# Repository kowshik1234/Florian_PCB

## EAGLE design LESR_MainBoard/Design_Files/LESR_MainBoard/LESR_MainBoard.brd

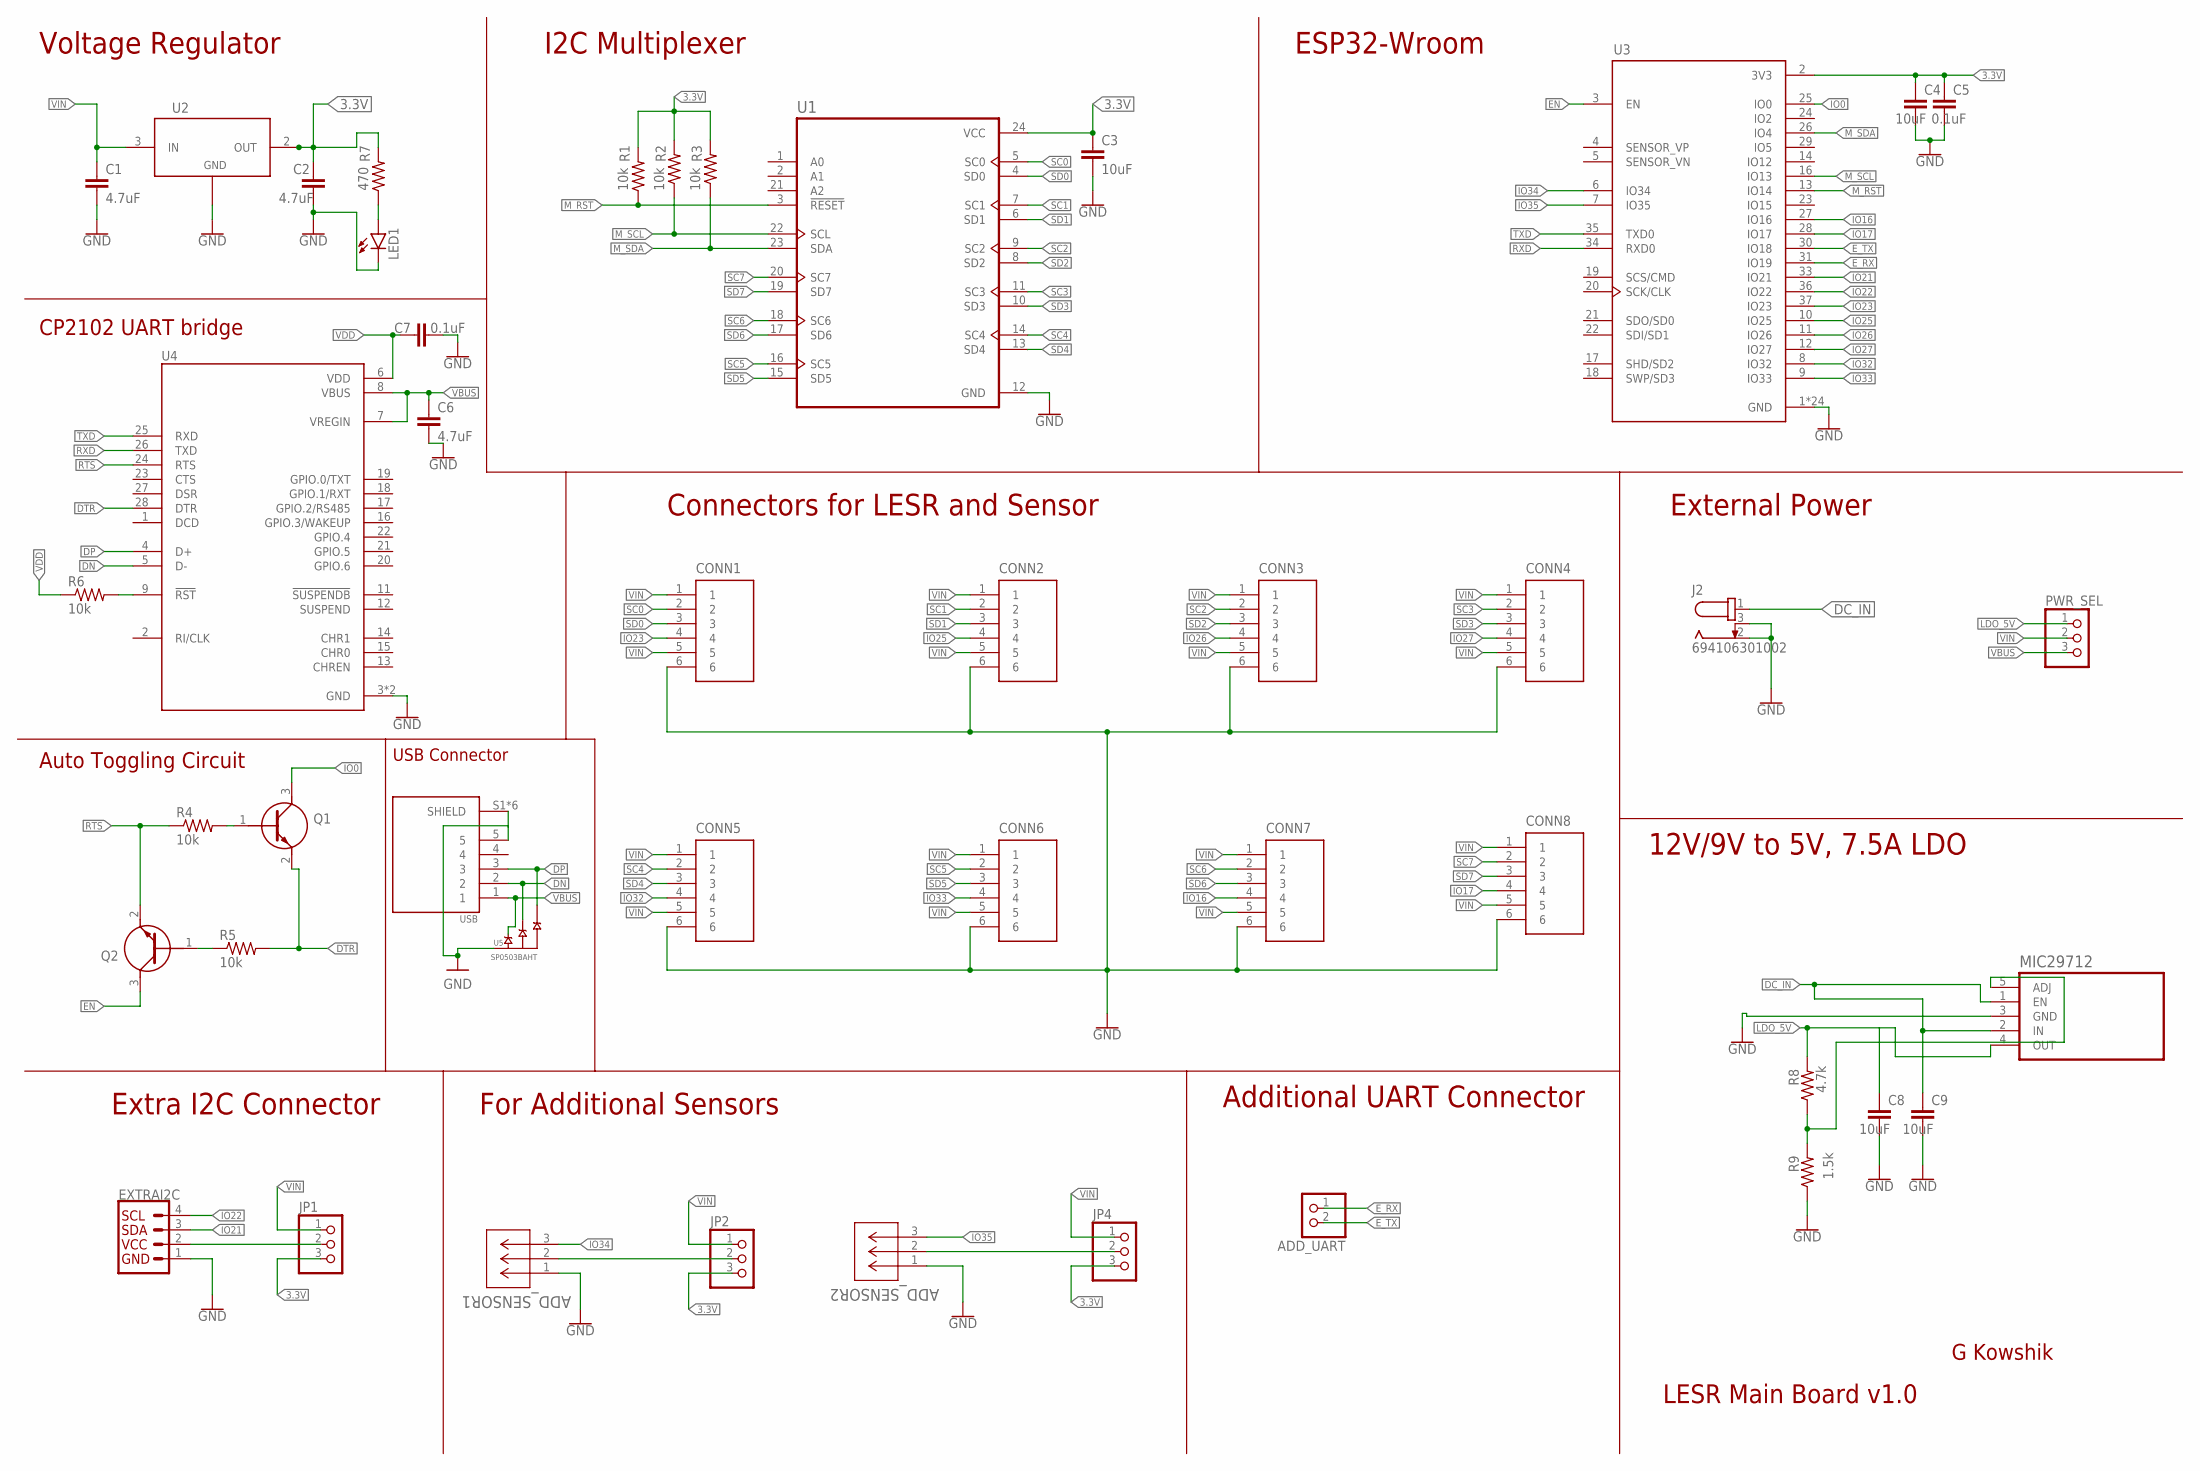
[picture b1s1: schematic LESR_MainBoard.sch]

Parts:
ADD_SENSOR1, ADD_SENSOR2: BM03B-SRSS-TB(LF)(SN); CONN_BM03B-SRSS-TB(LF)(SN)_JST
ADD_UART: JST_2PIN-SMT; JST-PH-2-SMT
C1, C2, C6: 4.7uF; C0805
C3, C4, C8, C9: 10uF; C0805
C5, C7: 0.1uF; C0805
CONN1, CONN2, CONN3, CONN4, CONN5, CONN6, CONN7, CONN8: JST_6_PIN_VERTICAL; JST-6-SMD-VERT-1.0MM
EXTRAI2C: Vertical Qwiic Connector; JST04_1MM_VERT
J2: 694106301002
JP1, JP2, JP4: PINHD-1X3; 1X03
LED1: LEDCHIPLED_0805; CHIPLED_0805
MIC29712: MIC29712WT; TO170P1066X482X1572-5
PWR_SEL: PINHD-1X3; 1X03
Q1, Q2: SS8050-G; SOT95P240X115-3N
R1, R2, R3, R4, R5, R6: 10k; R0805
R7: 470; R0805
R8: 4.7k; R0805
R9: 1.5k; R0805
U1: TCA9548APWR; SOP65P640X120-24N
U2: NCP1117ST33T3G; SOT-223
U3: ESP32-WROOM-32; MODULE_ESP32-WROOM-32
U4: CP2102N-A01-GQFN28; QFN50P500X500X80-29N
U5: SP0503BAHT; SOT143
USB: 10118194-0001LF; AMPHENOL_10118194-0001LF

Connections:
3.3V: C2.1, C3.1, C4.1, C5.1, JP1.3, JP2.3, JP4.3, R1.2, R2.2, R3.2, R7.2, U1.24 (VCC), U2.2 (OUT), U2.4, U3.2 (3V3)
DC_IN: C9.1, J2.1, MIC29712.1 (EN), MIC29712.2 (IN)
DN: U4.5 (D-), U5.3 (B), USB.2
DP: U4.4 (D+), U5.4 (C), USB.3
DTR: Q1.2 (E), R5.2, U4.28 (DTR)
EN: Q2.3 (C), U3.3 (EN)
E_RX: ADD_UART.1 (2), U3.31 (IO19)
E_TX: ADD_UART.2 (1), U3.30 (IO18)
GND: ADD_SENSOR1.1, ADD_SENSOR2.1, C1.2, C2.2, C3.2, C4.2, C5.2, C6.2, C7.2, C8.2, C9.2, CONN1.6, CONN2.6, CONN3.6, CONN4.6, CONN5.6, CONN6.6, CONN7.6, CONN8.6, EXTRAI2C.1, J2.2, J2.3, LED1.C, MIC29712.3 (GND), R9.1, U1.12 (GND), U2.1 (ADJ/GND), U3.1 (GND), U3.15 (GND), U3.38 (GND), U3.39_1 (GND), U3.39_2 (GND), U3.39_3 (GND), U3.39_4 (GND), U3.39_5 (GND), U3.39_6 (GND), U3.39_7 (GND), U3.39_8 (GND), U3.39_9 (GND), U3.39_10 (GND), U3.39_11 (GND), U3.39_12 (GND), U3.39_13 (GND), U3.39_14 (GND), U3.39_15 (GND), U3.39_16 (GND), U3.39_17 (GND), U3.39_18 (GND), U3.39_19 (GND), U3.39_20 (GND), U3.39_21 (GND), U4.3 (GND), U4.29 (GND), U5.1 (GND), USB.5, USB.S1 (SHIELD), USB.S2 (SHIELD), USB.S3 (SHIELD), USB.S4 (SHIELD), USB.S5 (SHIELD), USB.S6 (SHIELD)
IO0: Q1.3 (C), U3.25 (IO0)
IO16: CONN7.4, U3.27 (IO16)
IO17: CONN8.4, U3.28 (IO17)
IO21: EXTRAI2C.3, U3.33 (IO21)
IO22: EXTRAI2C.4, U3.36 (IO22)
IO23: CONN1.4, U3.37 (IO23)
IO25: CONN2.4, U3.10 (IO25)
IO26: CONN3.4, U3.11 (IO26)
IO27: CONN4.4, U3.12 (IO27)
IO32: CONN5.4, U3.8 (IO32)
IO33: CONN6.4, U3.9 (IO33)
IO34: ADD_SENSOR1.3, U3.6 (IO34)
IO35: ADD_SENSOR2.3, U3.7 (IO35)
LDO_5V: C8.1, MIC29712.4 (OUT), PWR_SEL.1, R8.2
M_RST: R1.1, U1.3 (!RESET), U3.13 (IO14)
M_SCL: R2.1, U1.22 (SCL), U3.16 (IO13)
M_SDA: R3.1, U1.23 (SDA), U3.26 (IO4)
unnamed: ADD_SENSOR1.2, JP2.2
unnamed: MIC29712.5 (ADJ), R8.1, R9.2
unnamed: Q1.1 (B), R4.2
unnamed: Q2.1 (B), R5.1
unnamed: ADD_SENSOR2.2, JP4.2
unnamed: R6.2, U4.9 (!RST)
unnamed: EXTRAI2C.2, JP1.2
unnamed: LED1.A, R7.1
RTS: Q2.2 (E), R4.1, U4.24 (RTS)
RXD: U3.34 (RXD0), U4.26 (TXD)
SC0: CONN1.2, U1.5 (SC0)
SC1: CONN2.2, U1.7 (SC1)
SC2: CONN3.2, U1.9 (SC2)
SC3: CONN4.2, U1.11 (SC3)
SC4: CONN5.2, U1.14 (SC4)
SC5: CONN6.2, U1.16 (SC5)
SC6: CONN7.2, U1.18 (SC6)
SC7: CONN8.2, U1.20 (SC7)
SD0: CONN1.3, U1.4 (SD0)
SD1: CONN2.3, U1.6 (SD1)
SD2: CONN3.3, U1.8 (SD2)
SD3: CONN4.3, U1.10 (SD3)
SD4: CONN5.3, U1.13 (SD4)
SD5: CONN6.3, U1.15 (SD5)
SD6: CONN7.3, U1.17 (SD6)
SD7: CONN8.3, U1.19 (SD7)
TXD: U3.35 (TXD0), U4.25 (RXD)
VBUS: C6.1, PWR_SEL.3, U4.7 (VREGIN), U4.8 (VBUS), U5.2 (A), USB.1
VDD: C7.1, R6.1, U4.6 (VDD)
VIN: C1.1, CONN1.1, CONN1.5, CONN2.1, CONN2.5, CONN3.1, CONN3.5, CONN4.1, CONN4.5, CONN5.1, CONN5.5, CONN6.1, CONN6.5, CONN7.1, CONN7.5, CONN8.1, CONN8.5, JP1.1, JP2.1, JP4.1, PWR_SEL.2, U2.3 (IN)

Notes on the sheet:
Voltage Regulator
LESR Main Board v1.0
G Kowshik
I2C Multiplexer
ESP32-Wroom
CP2102 UART bridge
Auto Toggling Circuit
USB Connector
Extra I2C Connector
For Additional Sensors
Additional UART Connector
External Power
Connectors for LESR and Sensor
12V/9V to 5V, 7.5A LDO

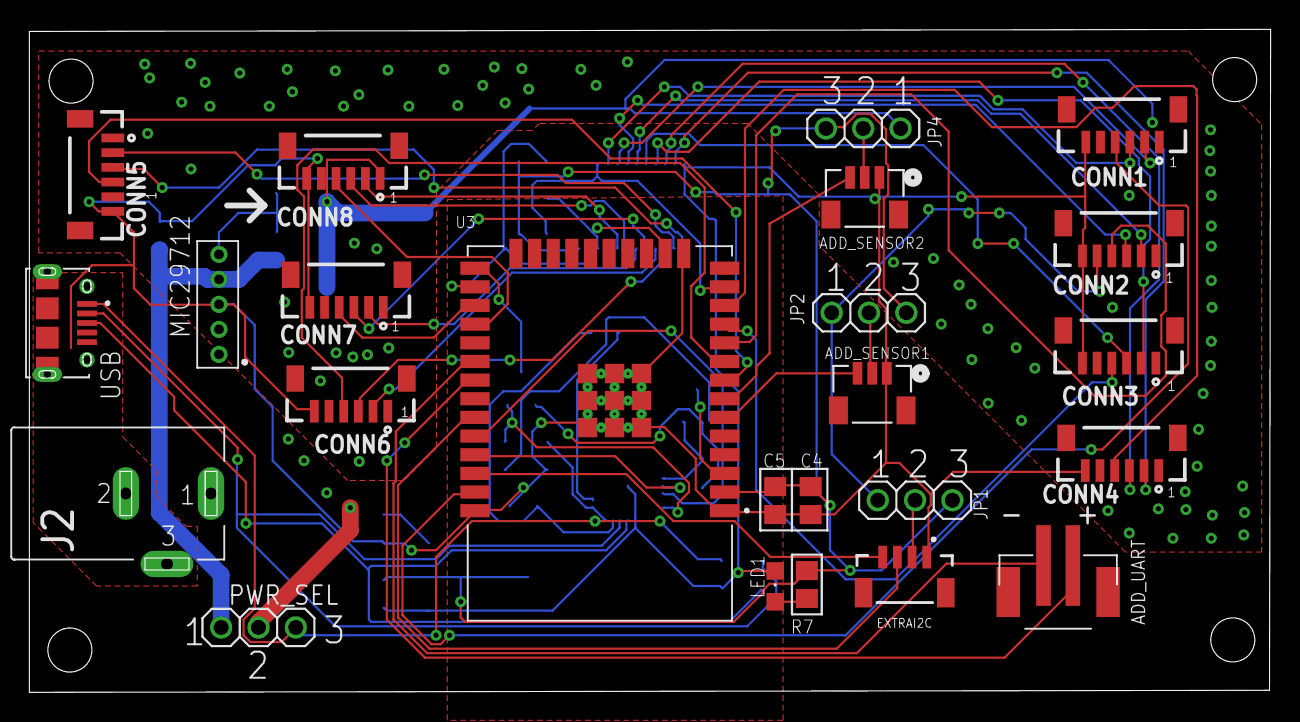
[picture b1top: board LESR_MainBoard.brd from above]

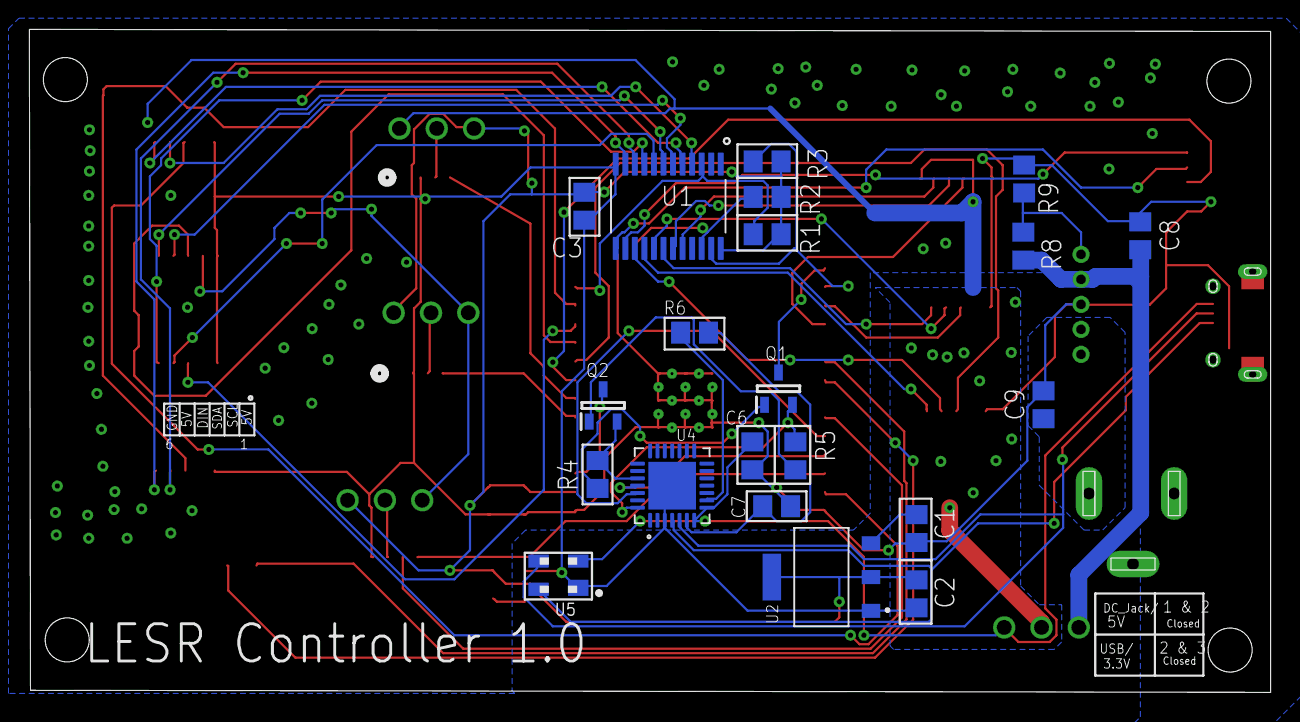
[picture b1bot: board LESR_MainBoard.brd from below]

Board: 2 copper layers, 84.5 x 45.1 mm, 45 parts (21 on the bottom side), 56 nets.

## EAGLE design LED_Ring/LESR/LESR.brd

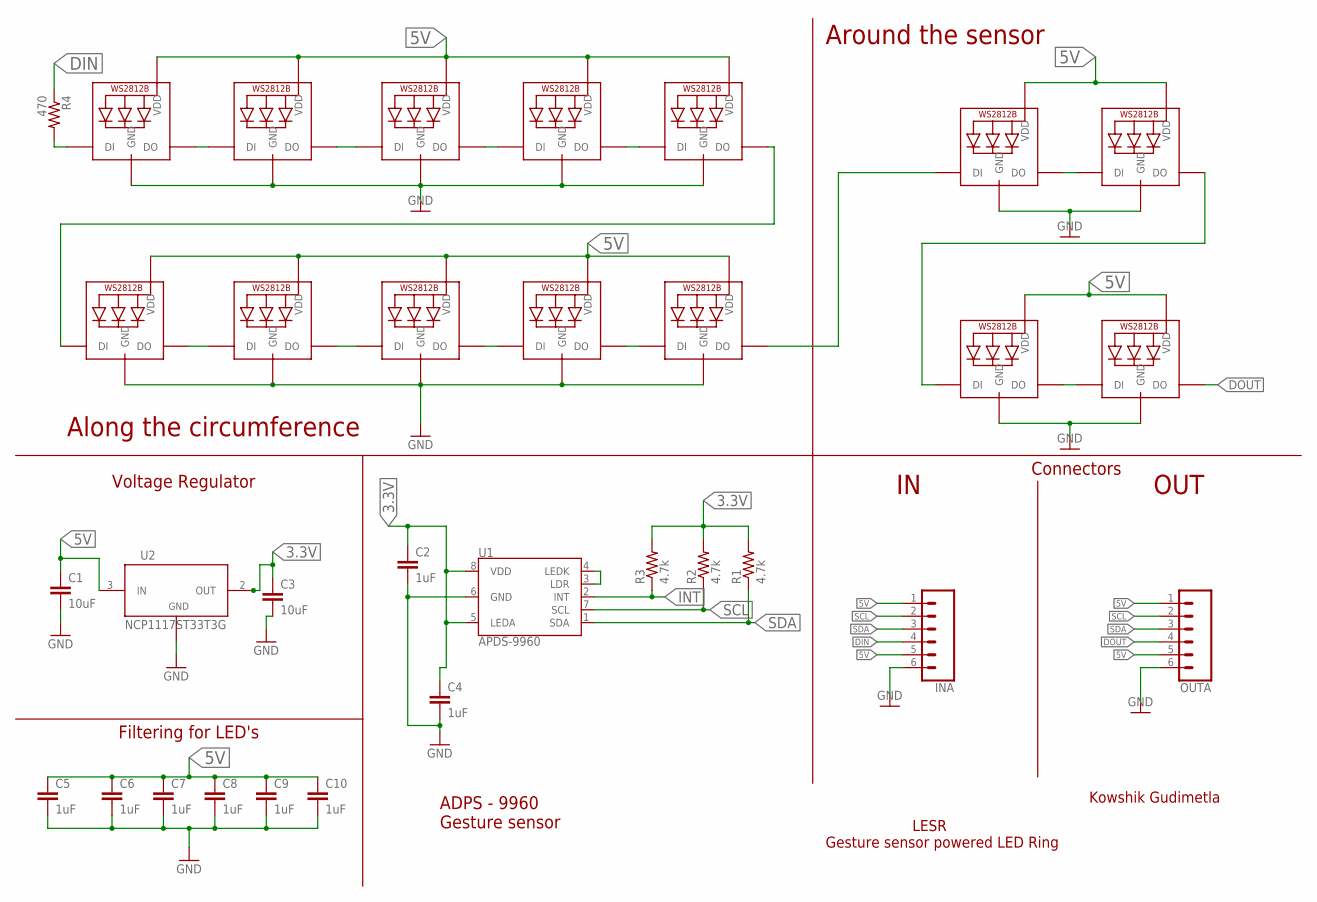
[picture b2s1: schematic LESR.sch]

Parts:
C1, C3: 10uF; C0603
C2, C4, C5, C6, C7, C8, C9, C10: 1uF; C0603
IN: BM06B-SRSS-TB; JST-6-SMD-HORI-1.0MM
LED1, LED2, LED3, LED4, LED5, LED6, LED7, LED8, LED9, LED10, LED11, LED12, LED13, LED14: WS2812B5050; WS2812B
OUT: BM06B-SRSS-TB; JST-6-SMD-HORI-1.0MM
R1, R2, R3: 4.7k; R0603
R4: 470; R0603
U1: APDS-9960
U2: NCP1117ST33T3G; SOT-223

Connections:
3.3V: C2.1, C3.1, C4.1, R1.2, R2.2, R3.2, U1.5 (LEDA), U1.8 (VDD), U2.2 (OUT), U2.4
5V: C1.1, C5.1, C6.1, C7.1, C8.1, C9.1, C10.1, IN.1, IN.5, LED1.1-VDD (VDD), LED2.1-VDD (VDD), LED3.1-VDD (VDD), LED4.1-VDD (VDD), LED5.1-VDD (VDD), LED6.1-VDD (VDD), LED7.1-VDD (VDD), LED8.1-VDD (VDD), LED9.1-VDD (VDD), LED10.1-VDD (VDD), LED11.1-VDD (VDD), LED12.1-VDD (VDD), LED13.1-VDD (VDD), LED14.1-VDD (VDD), OUT.1, OUT.5, U2.3 (IN)
DIN: IN.4, R4.1
DOUT: LED14.2-DOUT (DO), OUT.4
GND: C1.2, C2.2, C3.2, C4.2, C5.2, C6.2, C7.2, C8.2, C9.2, C10.2, IN.6, LED1.3-GND (GND), LED2.3-GND (GND), LED3.3-GND (GND), LED4.3-GND (GND), LED5.3-GND (GND), LED6.3-GND (GND), LED7.3-GND (GND), LED8.3-GND (GND), LED9.3-GND (GND), LED10.3-GND (GND), LED11.3-GND (GND), LED12.3-GND (GND), LED13.3-GND (GND), LED14.3-GND (GND), OUT.6, U1.6 (GND), U2.1 (ADJ/GND)
INT: R3.1, U1.2 (INT)
unnamed: LED1.4-DIN (DI), R4.2
unnamed: U1.3 (LDR), U1.4 (LEDK)
unnamed: LED6.2-DOUT (DO), LED7.4-DIN (DI)
unnamed: LED7.2-DOUT (DO), LED8.4-DIN (DI)
unnamed: LED8.2-DOUT (DO), LED9.4-DIN (DI)
unnamed: LED9.2-DOUT (DO), LED10.4-DIN (DI)
unnamed: LED1.2-DOUT (DO), LED2.4-DIN (DI)
unnamed: LED2.2-DOUT (DO), LED3.4-DIN (DI)
unnamed: LED3.2-DOUT (DO), LED4.4-DIN (DI)
unnamed: LED4.2-DOUT (DO), LED5.4-DIN (DI)
unnamed: LED11.2-DOUT (DO), LED12.4-DIN (DI)
unnamed: LED13.2-DOUT (DO), LED14.4-DIN (DI)
unnamed: LED12.2-DOUT (DO), LED13.4-DIN (DI)
unnamed: LED5.2-DOUT (DO), LED6.4-DIN (DI)
unnamed: LED10.2-DOUT (DO), LED11.4-DIN (DI)
SCL: IN.2, OUT.2, R2.1, U1.7 (SCL)
SDA: IN.3, OUT.3, R1.1, U1.1 (SDA)

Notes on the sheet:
Kowshik Gudimetla
LESR Gesture sensor powered LED Ring
Voltage Regulator
ADPS - 9960 Gesture sensor
Along the circumference
Around the sensor
Connectors
Filtering for LED's
OUT

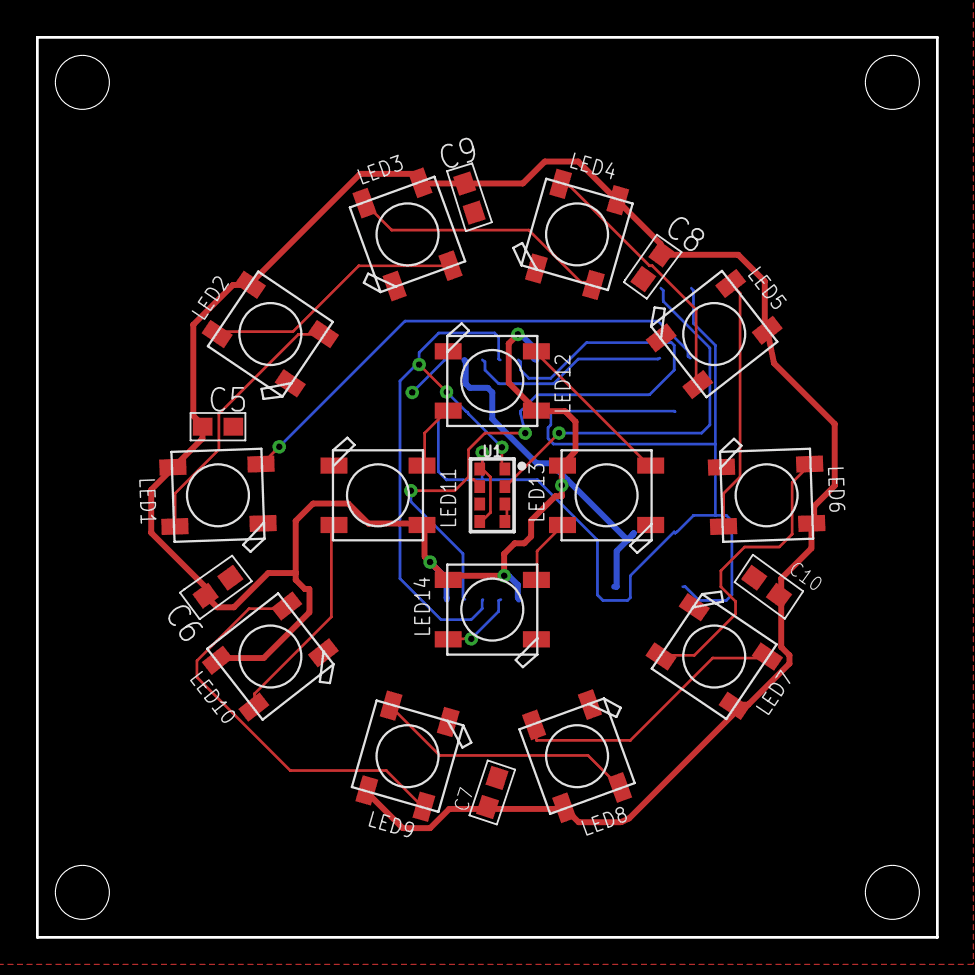
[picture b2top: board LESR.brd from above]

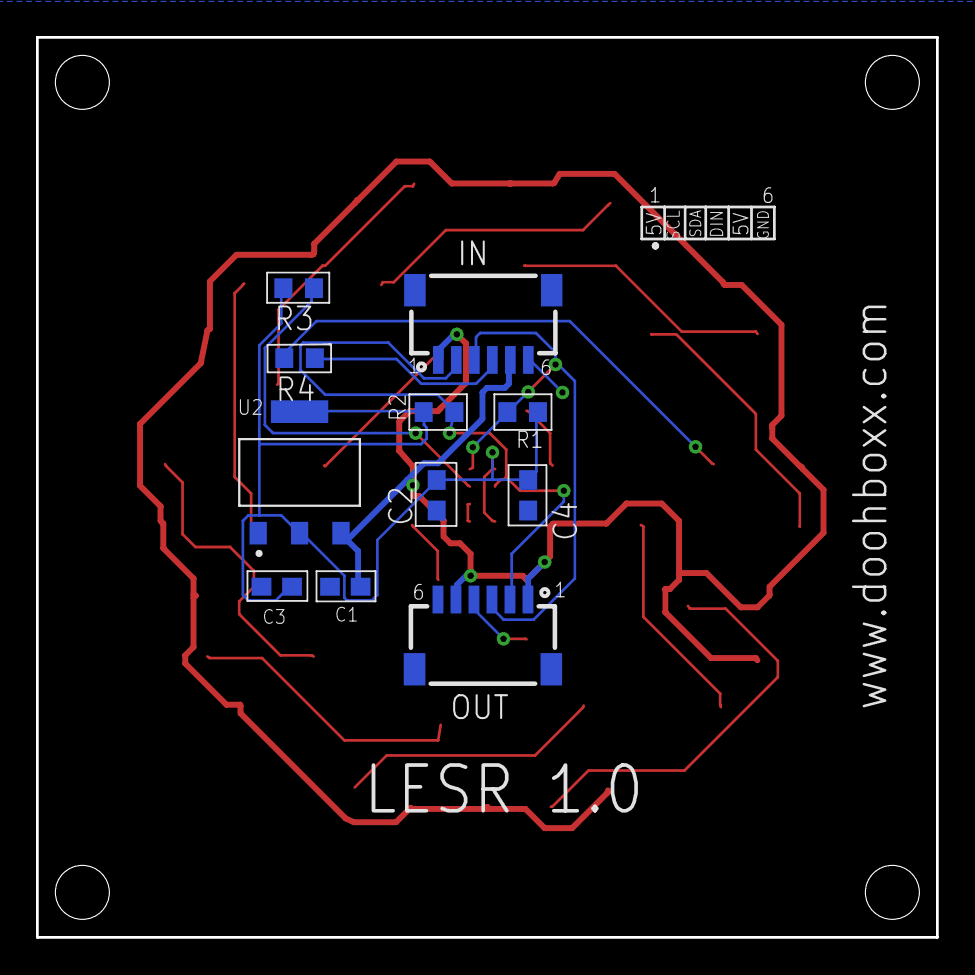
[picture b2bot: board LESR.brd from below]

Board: 2 copper layers, 50.0 x 50.0 mm, 32 parts (11 on the bottom side), 23 nets.

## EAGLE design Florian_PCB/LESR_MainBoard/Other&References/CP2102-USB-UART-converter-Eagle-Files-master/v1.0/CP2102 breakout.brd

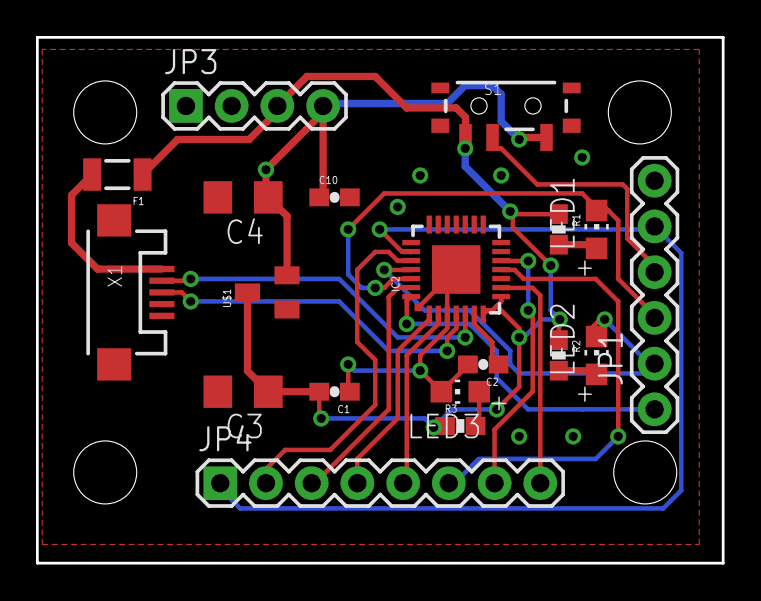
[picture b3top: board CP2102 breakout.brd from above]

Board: 2 copper layers, 38.1 x 29.2 mm, 23 parts (0 on the bottom side), 22 nets.

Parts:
C1, C2, C10: 100nF; 0603-CAP
C3: 10uF; C3216
C4: 22uF; C3216
F1: PTCSMD; PTC-1206
IC2: CP210X_USB_UART; MLP28
JP1: FTDI_BASICPTH; FTDI_BASIC
JP3: 1X04
JP4: 1X08
LED1: bijela; CHIP-LED0805
LED2: crvena; CHIP-LED0805
LED3: plava; CHIP-LED0805
R1, R2, R3: 680; 0603-RES
S1: SWITCH-SPST-SMD-A
U$1: 622K; 662K
U$2: OSH3MM
U$3: NOVI_LOGO-4MM
U$4: LUDI_LOGO_BACK
U$5: E-RADIONICA.COM_MADE_IN_BACK!
X1: USB-MICROB

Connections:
3.3V: C4.1, C10.1, JP3.4, S1.3, U$1.OUT
+5V: C1.2, C3.1, F1.1, IC2.7, IC2.8, JP3.3, R1.1, R2.1, R3.1, S1.1, U$1.IN
CTS: IC2.23, JP1.CTS, JP4.1
D+: IC2.4, X1.D+
D-: IC2.5, X1.D-
DCD: IC2.1, JP4.4
DSR: IC2.27, JP4.3
DTR: IC2.28, JP1.DTR
GND: C1.1, C2.2, C3.2, C4.2, C10.2, IC2.3, IC2.EXP, IC2.M, JP1.GND, JP3.1, JP3.2, LED3.C, U$1.GND, X1.GND
unnamed: LED1.A, R1.2
unnamed: LED2.A, R2.2
unnamed: LED3.A, R3.2
unnamed: C2.1, IC2.6
RI: IC2.2, JP4.5
RST: IC2.9, JP4.8
RTS: IC2.24, JP4.2
RXD: IC2.25, JP1.RXI, LED2.C
SUSPEND: IC2.12, JP4.7
SUSPEND': IC2.11, JP4.6
TXD: IC2.26, JP1.TXO, LED1.C
VBUS: F1.2, X1.VBUS
VCC: JP1.VCC, S1.2

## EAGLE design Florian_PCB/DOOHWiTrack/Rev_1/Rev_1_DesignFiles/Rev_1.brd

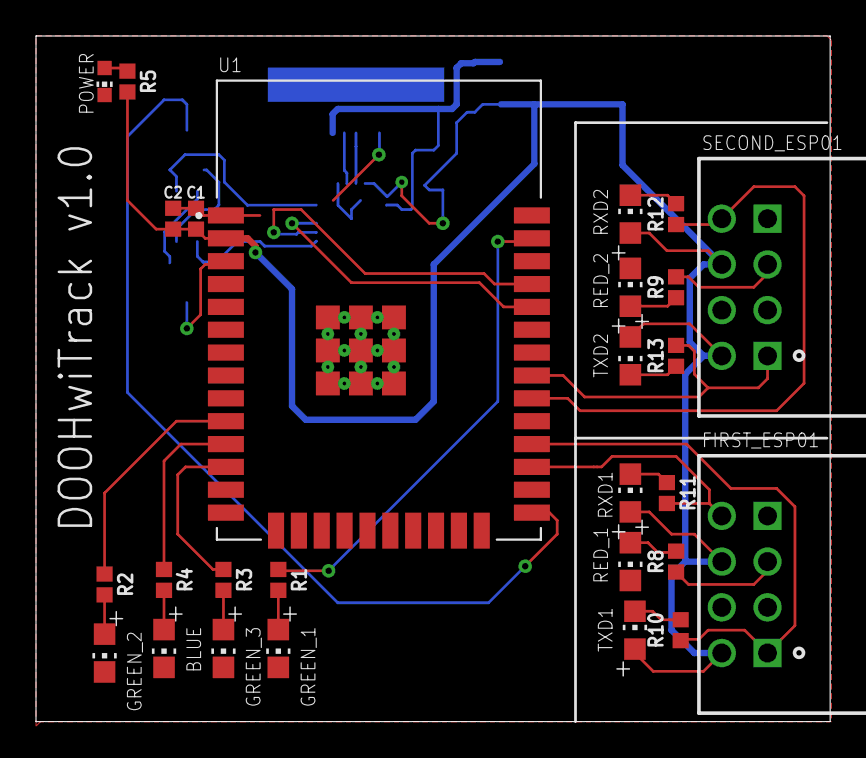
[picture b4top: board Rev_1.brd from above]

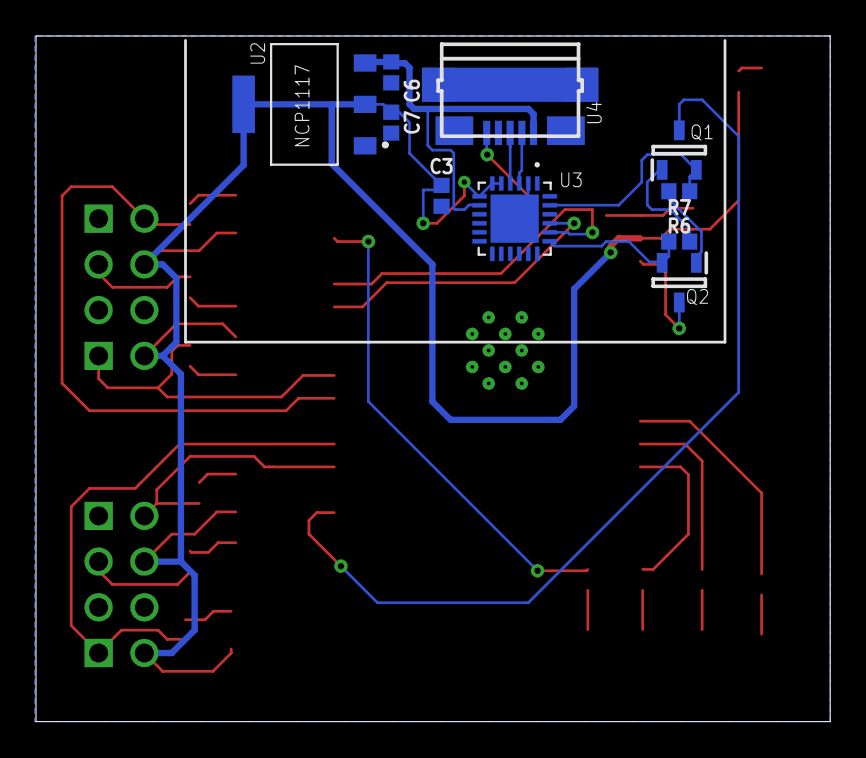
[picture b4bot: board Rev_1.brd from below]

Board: 2 copper layers, 44.1 x 38.1 mm, 37 parts (10 on the bottom side), 34 nets.

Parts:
BLUE: CHIP-LED0805
C1, C3, C6, C7: 10uF; 0402
C2: 0.1uF; 0402
FIRST_ESP01: ESP8266-01/ESP-01; XCVR_ESP8266-01/ESP-01
GREEN_1, GREEN_2, GREEN_3: CHIP-LED0805
POWER: CHIP-LED0603
Q1, Q2: SS8050-G; SOT95P240X115-3N
R1, R2, R3, R4, R8, R9, R10, R11, R12, R13: 100; 0402
R5: 470; 0402
R6, R7: 10k; 0402
RED_1, RED_2: CHIP-LED0805
RXD1, RXD2: CHIP-LED0805
SECOND_ESP01: ESP8266-01/ESP-01; XCVR_ESP8266-01/ESP-01
TXD1, TXD2: CHIP-LED0805
U1: ESP32-WROOM-32; MODULE_ESP32-WROOM-32
U2: NCP1117ST33T3G; SOT-223
U3: CP2104-F03-GM; QFN50P400X400X80-25N
U4: J_USB_MICROAB_HIROSE_ZX62-AB-5PA

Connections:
1ESP01_IO2: FIRST_ESP01.3, R8.1
2ESP01_IO2: R9.1, SECOND_ESP01.3
3.3V_OUT: C1.1, C2.1, C3.1, C7.1, FIRST_ESP01.6, FIRST_ESP01.8, R5.2, RXD1.A, RXD2.A, SECOND_ESP01.6, SECOND_ESP01.8, TXD1.A, TXD2.A, U1.2, U2.2, U2.4, U3.5, U3.6, U3.7
DN: U3.4, U4.P$3
DP: U3.3, U4.P$2
DTR: Q1.2, R7.2, U3.23
EN: Q2.3, U1.3
ESP_RXD: U1.34, U3.21
ESP_TXD: U1.35, U3.20
GND: BLUE.C, C1.2, C2.2, C3.2, C6.2, C7.2, FIRST_ESP01.4, GREEN_1.C, GREEN_2.C, GREEN_3.C, POWER.C, RED_1.C, RED_2.C, SECOND_ESP01.4, U1.1, U1.15, U1.38, U1.39_1, U1.39_2, U1.39_3, U1.39_4, U1.39_5, U1.39_6, U1.39_7, U1.39_8, U1.39_9, U1.39_10, U1.39_11, U1.39_12, U1.39_13, U1.39_14, U1.39_15, U1.39_16, U1.39_17, U1.39_18, U1.39_19, U1.39_20, U1.39_21, U2.1, U3.2, U3.25, U4.P$5
IO0: Q1.3, U1.25
LED1: R1.1, U1.37
LED2: R2.1, U1.10
LED3: R4.1, U1.11
LED4: R3.1, U1.12
LED_RXD1: FIRST_ESP01.5, R11.2, U1.27
LED_RXD2: R12.2, SECOND_ESP01.5, U1.30
LED_TXD1: FIRST_ESP01.1, R10.2, U1.28
LED_TXD2: R13.2, SECOND_ESP01.1, U1.31
unnamed: GREEN_1.A, R1.2
unnamed: GREEN_2.A, R2.2
unnamed: GREEN_3.A, R3.2
unnamed: BLUE.A, R4.2
unnamed: POWER.A, R5.1
unnamed: R8.2, RED_1.A
unnamed: Q1.1, R6.2
unnamed: Q2.1, R7.1
unnamed: R9.2, RED_2.A
unnamed: R10.1, TXD1.C
unnamed: R12.1, RXD2.C
unnamed: R13.1, TXD2.C
unnamed: R11.1, RXD1.C
RTS: Q2.2, R6.1, U3.19
V_USB: C6.1, U2.3, U3.8, U4.P$1

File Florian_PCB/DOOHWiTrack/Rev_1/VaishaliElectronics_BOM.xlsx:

Bill Of Materials (BOM) |  |  | DOOHwiTrack V1.0
Item # | *Designator | *Qty | Manufacturer | *Mfg Part # | Description / Value | *Package/Footprint | Type | Digi-Key Link (For Reference Only)
1 | U1 | 2 | Espressif Systems | ESP32-WROOM-32 | Bluetooth, WiFi Transceiver Module 2.4GHz ~ 2.5GHz Surface Mount | 38pin-SMD Module | SMD | https://www.digikey.in/short/z4h8n9
2 | U2 | 3 | ON Semiconductor | NCP1117ST33T3G | IC REG LINEAR 3.3V 1A SOT223 | TO-261-4, TO-261AA | SMD | https://www.digikey.in/short/z4h8n0
3 | U3 | 2 | Silicon Labs | CP2104-F03-GMR | IC SGL USB-TO-UART BRIDGE 24QFN | 24-WFQFN Exposed Pad | SMD | https://www.digikey.in/short/z4h8d7
4 | U4 | 2 | Hirose Electric Co Ltd | ZX62-AB-5PA(31) | CONN RCPT USB2.0 MICRO AB SMD RA | Surface Mount | SMD | https://www.digikey.in/short/z4h8d4
5 | Q1, Q2 | 4 | Comchip Technology | SS8050-G | NPN TRANSISTOR 1.5A 40V SOT-23 R | SOT-23-3 | SMD | https://www.digikey.in/short/z4h809
6 | C1, C3, C6, C7 | 6 | KEMET | C0402C106M9PAC7411 | CAP CER 10UF 6.3V X5R 0402 | 0402 (1005 Metric) | SMD | https://www.digikey.com/short/z4hjp5
7 | C2 | 2 | KEMET | C0402C104M9PACTU | CAP CER 0.1UF 6.3V X5R 0402 | 0402 (1005 Metric) | SMD | https://www.digikey.in/short/z4hjbq
8 | R5 | 1 | Yageo | RC0402JR-07470RL | RES SMD 470 OHM 5% 1/16W 0402 | 0402 (1005 Metric) | SMD | https://www.digikey.in/short/z4hjwh
9 | R1, R2, R3, R4, R8, R9, R10, R11, R12, R13 | 10 | Yageo | RC0402JR-07100RL | RES SMD 100 OHM 5% 1/16W 0402 | 0402 (1005 Metric) | SMD | https://www.digikey.in/short/z4hj1z
10 | R6, R7 | 4 | Yageo | RC0402JR-0710KL | RES SMD 10K OHM 5% 1/16W 0402 | 0402 (1005 Metric) | SMD | https://www.digikey.in/short/z4hpc0
12 | POWER, RED_1, RED_2 | 3 | Dialight | 5988120107F | LED RED CLEAR 0805 SMD | 0805 (2012 Metric) | SMD | https://www.digikey.com/short/z4hpft
13 | GREEN_1, GREEN_2, GREEN_3 | 3 | Dialight | 5988170107F | LED GREEN CLEAR 0805 SMD | 0805(2012 Metric) | SMD | https://www.digikey.com/short/z4hpnz
14 | RXD_1, RXD_2, TXD_1, TXD_2, BLUE | 5 | Dialight | 5988191102F | LED BLUE CLEAR 0805 SMD | 0805(2012 Metric) | SMD | https://www.digikey.com/short/z4hztj
 | Note: All the above components are for reference only and need NOT to be essent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

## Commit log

2020-06-23 LESR Ring files
2020-06-23 Reuploading
2020-06-23 Now do it
2020-06-23 Final Files
2020-06-28 JST Updated in Main B
2020-06-30 Update Commit due to LESR Ring
2020-06-30 Updated due to LESR Ring connector
2020-06-30 Update - LESR Ring connector
2020-07-25 12V to 5V LDO version
2020-08-07 Controller dimensions changed

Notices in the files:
parts and their libraries:
SparkFun-Capacitors: Licensing: Creative Commons ShareAlike 4.0 International - https://creativecommons.org/licenses/by-sa/4.0
SparkFun: Licensing: CC v3.0 Share-Alike You are welcome to use this library for commercial purposes.
COPYRIGHT: Copyright (C) 2018 Accelerated Designs. All rights reserved
